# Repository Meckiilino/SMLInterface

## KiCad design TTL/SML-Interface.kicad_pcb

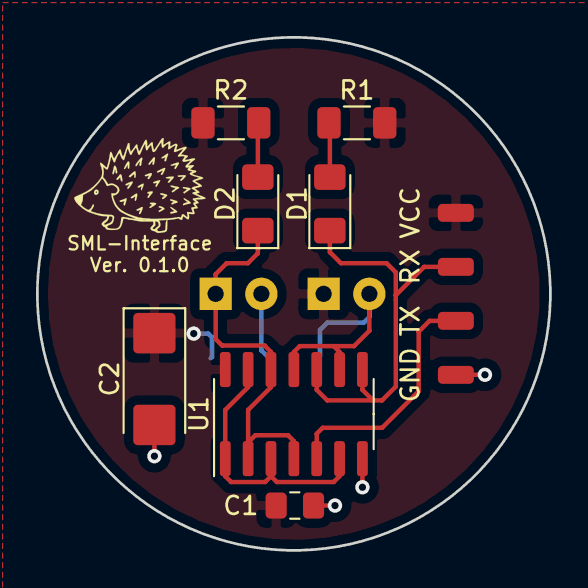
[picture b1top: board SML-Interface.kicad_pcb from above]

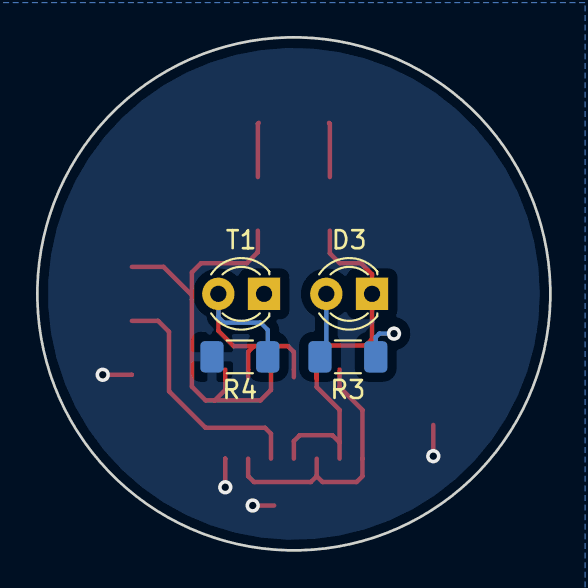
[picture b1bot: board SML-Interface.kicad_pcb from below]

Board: 2 copper layers, 28.5 x 28.5 mm, 15 parts (4 on the bottom side), 10 nets.

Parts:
C1: 100n; C_0805_2012Metric_Pad1.18x1.45mm_HandSolder
C2: 22µ; CP_EIA-6032-15_Kemet-U_Pad2.25x2.35mm_HandSolder
D1: RX-LED (gn); LED_1206_3216Metric_Pad1.42x1.75mm_HandSolder
D2: TX-LED (rt); LED_1206_3216Metric_Pad1.42x1.75mm_HandSolder
D3: SFH4350; LED_D3.0mm_Clear
GND: Conn_01x01; SolderWirePad_1x01_SMD_1x2mm
R1, R2, R3: 180R; R_1206_3216Metric_Pad1.30x1.75mm_HandSolder
R4: 10K; R_1206_3216Metric_Pad1.30x1.75mm_HandSolder
RX: Conn_01x01; SolderWirePad_1x01_SMD_1x2mm
T1: SFH309; LED_D3.0mm_Clear
TX: Conn_01x01; SolderWirePad_1x01_SMD_1x2mm
U1: 74HC14; SO-14_3.9x8.65mm_P1.27mm
VCC: Conn_01x01; SolderWirePad_1x01_SMD_1x2mm

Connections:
GND: C1.1, C2.2, GND.1, R4.2, U1.7
unnamed: D1.1, RX.1, U1.8, U1.10
unnamed: D1.2, R1.2
unnamed: D2.1, D3.1, U1.2, U1.4, U1.12
unnamed: D2.2, R2.2
unnamed: D3.2, R3.2
unnamed: R4.1, T1.2, U1.9, U1.11
unnamed: TX.1, U1.5
unnamed: U1.1, U1.3, U1.6, U1.13
VCC: C1.2, C2.1, R1.1, R2.1, R3.1, T1.1, U1.14, VCC.1
